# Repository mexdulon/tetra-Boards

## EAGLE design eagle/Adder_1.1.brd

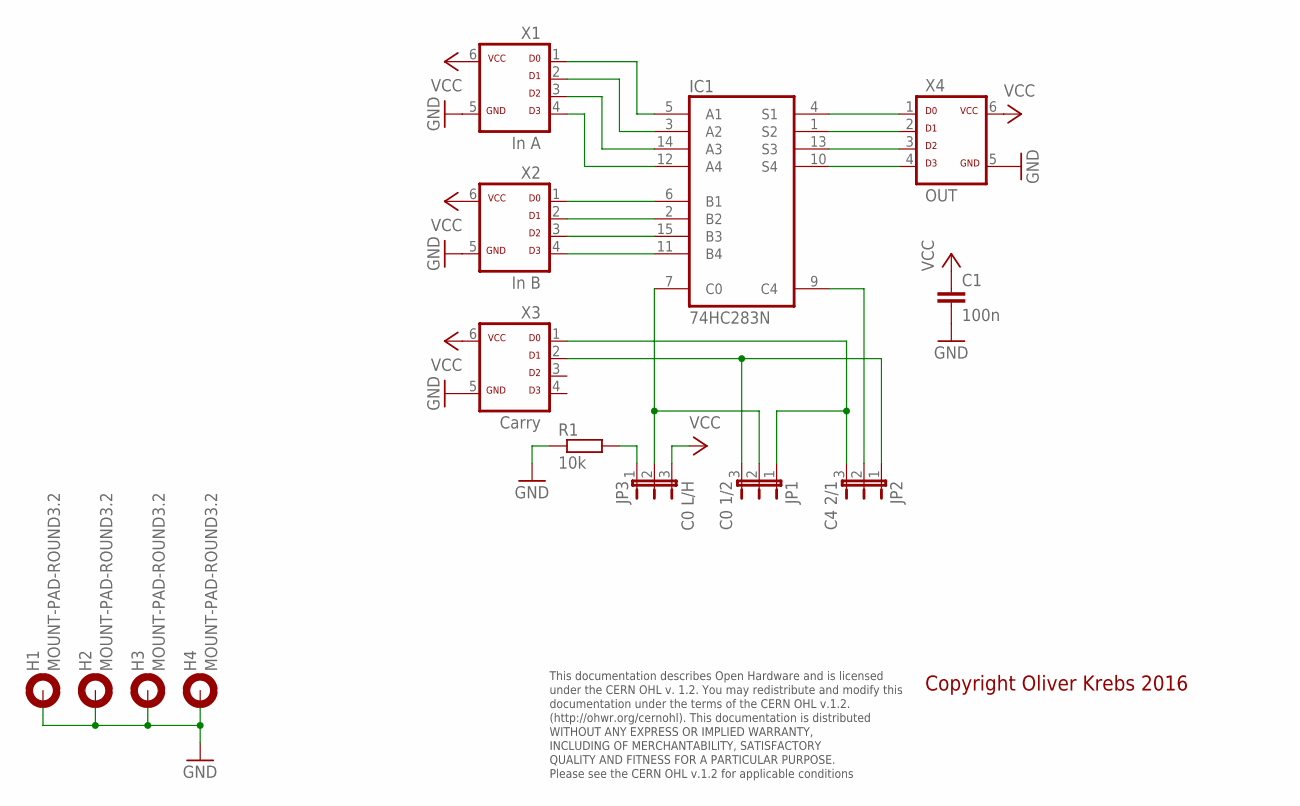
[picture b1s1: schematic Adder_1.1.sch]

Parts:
C1: 100n; C050-025X075
H1, H2, H3, H4: MOUNT-PAD-ROUND3.2; 3,2-PAD
IC1: 74HC283N; DIL16
JP1: C0 1/2; JP2
JP2: C4 2/1; JP2
JP3: C0 L/H; JP2
R1: 10k; 0207/10
X1: In A; ML-6
X2: In B; ML-6
X3: Carry; ML-6
X4: OUT; ML-6

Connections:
GND: C1.2, H1.B3,2, H2.B3,2, H3.B3,2, H4.B3,2, IC1.8 (GND), R1.1, X1.5, X2.5, X3.5, X4.5
unnamed: JP3.1, R1.2
unnamed: IC1.15 (B3), X2.3
unnamed: IC1.3 (A2), X1.2
unnamed: IC1.2 (B2), X2.2
unnamed: IC1.14 (A3), X1.3
unnamed: IC1.11 (B4), X2.4
unnamed: IC1.1 (S2), X4.2
unnamed: IC1.4 (S1), X4.1
unnamed: IC1.13 (S3), X4.3
unnamed: IC1.10 (S4), X4.4
unnamed: IC1.7 (C0), JP1.2, JP3.2
unnamed: IC1.9 (C4), JP2.2
unnamed: JP1.1, JP2.3, X3.1
unnamed: JP1.3, JP2.1, X3.2
unnamed: IC1.5 (A1), X1.1
unnamed: IC1.12 (A4), X1.4
unnamed: IC1.6 (B1), X2.1
VCC: C1.1, IC1.16 (VCC), JP3.3, X1.6, X2.6, X3.6, X4.6

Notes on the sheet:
This documentation describes Open Hardware and is licensed under the CERN OHL v. 1.2. You may redistribute and modify this documentation under the terms of the CERN OHL v.1.2. (http://ohwr.org/cernohl). This documentation is distributed WITHOUT ANY EXPRESS OR IMPLIED WARRANTY, INCLUDING OF MERCHANT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
Copyright Oliver Krebs 2016

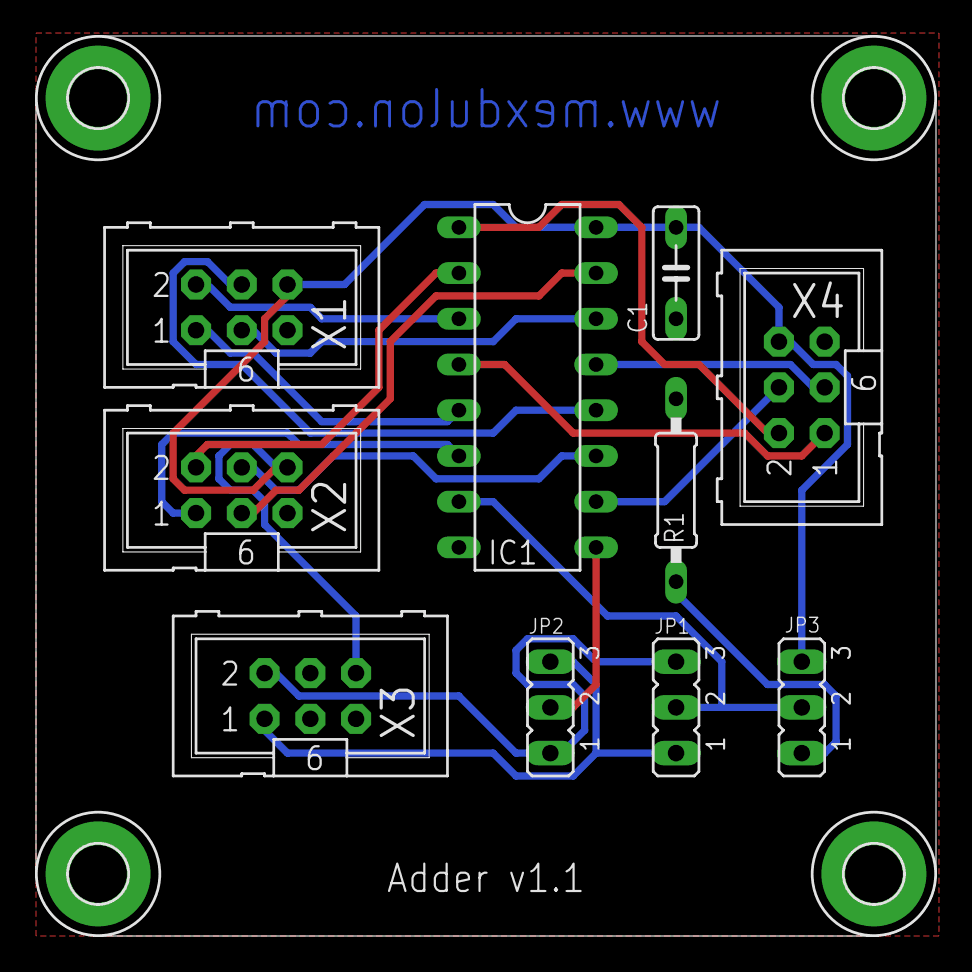
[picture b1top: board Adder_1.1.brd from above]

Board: 2 copper layers, 50.0 x 50.0 mm, 14 parts (0 on the bottom side), 19 nets.

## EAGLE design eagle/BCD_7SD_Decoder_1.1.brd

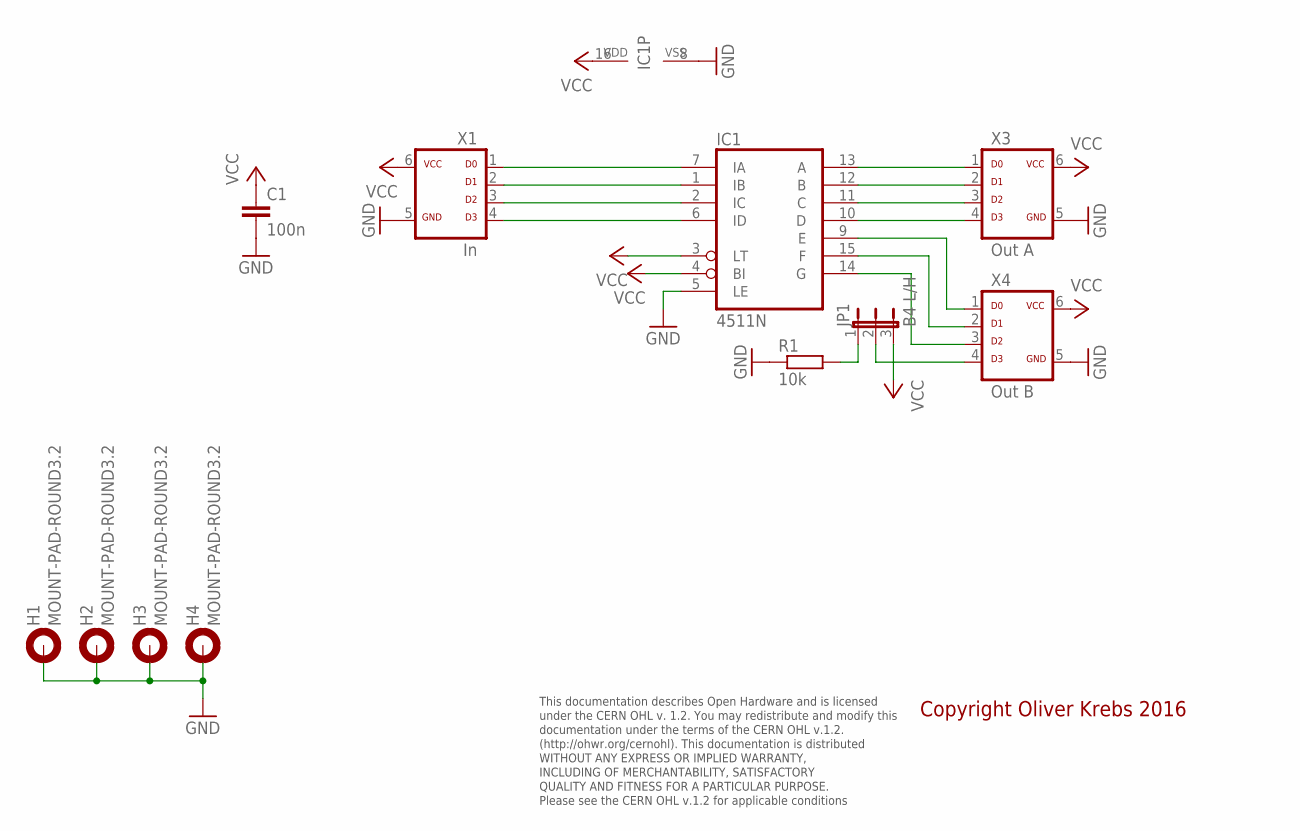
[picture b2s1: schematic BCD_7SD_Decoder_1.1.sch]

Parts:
C1: 100n; C050-025X075
H1, H2, H3, H4: MOUNT-PAD-ROUND3.2; 3,2-PAD
IC1: 4511N; DIL16
JP1: B4 L/H; JP2
R1: 10k; 0207/10
X1: In; ML-6
X3: Out A; ML-6
X4: Out B; ML-6

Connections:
GND: C1.2, H1.B3,2, H2.B3,2, H3.B3,2, H4.B3,2, IC1.5 (LE), IC1.8 (VSS), R1.1, X1.5, X3.5, X4.5
unnamed: IC1.7 (IA), X1.1
unnamed: IC1.1 (IB), X1.2
unnamed: IC1.2 (IC), X1.3
unnamed: IC1.6 (ID), X1.4
unnamed: IC1.13 (A), X3.1
unnamed: IC1.12 (B), X3.2
unnamed: IC1.11 (C), X3.3
unnamed: IC1.10 (D), X3.4
unnamed: IC1.9 (E), X4.1
unnamed: IC1.15 (F), X4.2
unnamed: IC1.14 (G), X4.3
unnamed: JP1.2, X4.4
unnamed: JP1.1, R1.2
VCC: C1.1, IC1.3 (LT), IC1.4 (BI), IC1.16 (VDD), JP1.3, X1.6, X3.6, X4.6

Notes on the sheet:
This documentation describes Open Hardware and is licensed under the CERN OHL v. 1.2. You may redistribute and modify this documentation under the terms of the CERN OHL v.1.2. (http://ohwr.org/cernohl). This documentation is distributed WITHOUT ANY EXPRESS OR IMPLIED WARRANTY, INCLUDING OF MERCHANT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
Copyright Oliver Krebs 2016

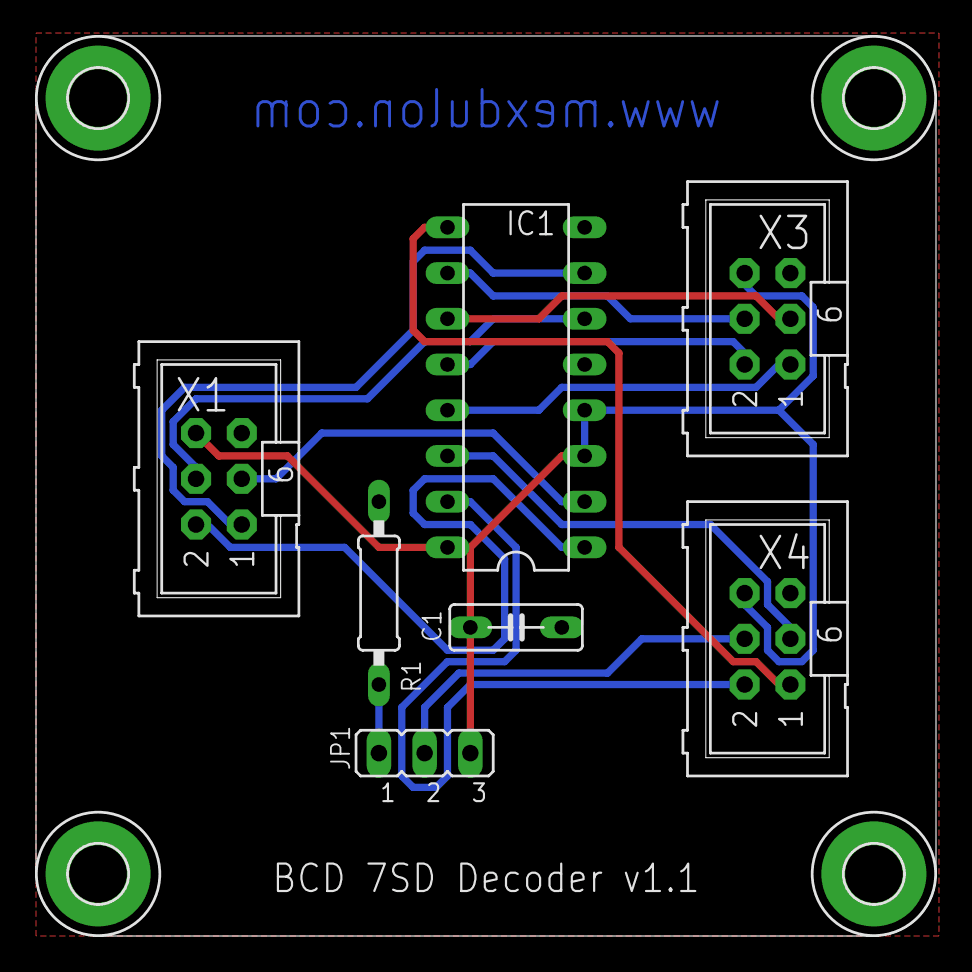
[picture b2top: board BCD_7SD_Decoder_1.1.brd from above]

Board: 2 copper layers, 50.0 x 50.0 mm, 11 parts (0 on the bottom side), 15 nets.

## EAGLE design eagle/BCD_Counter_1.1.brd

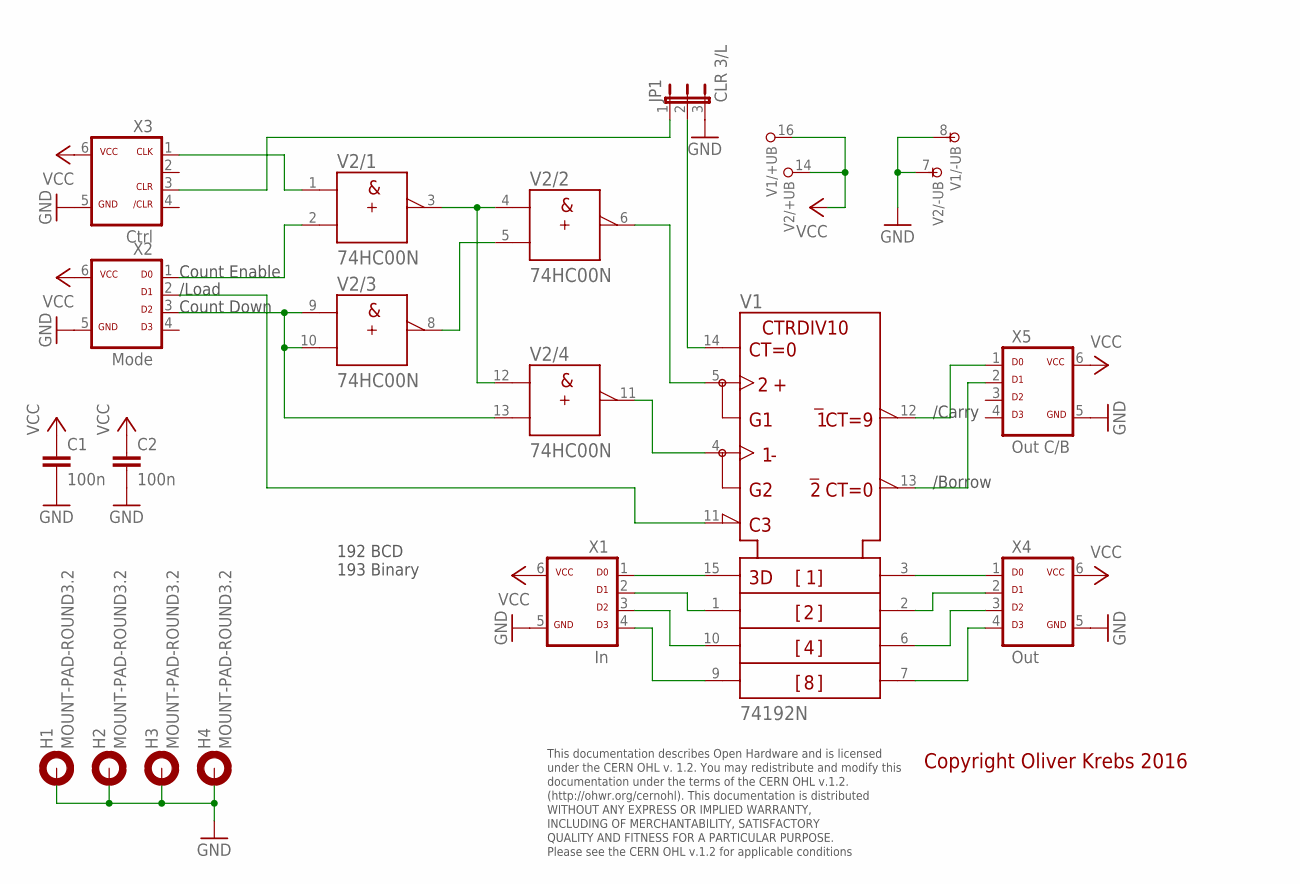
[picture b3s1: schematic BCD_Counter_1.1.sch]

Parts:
C1, C2: 100n; C050-025X075
H1, H2, H3, H4: MOUNT-PAD-ROUND3.2; 3,2-PAD
JP1: CLR 3/L; JP2
V1: 74192N; DIL16
V2: 74HC00N; DIL14
X1: In; ML-6
X2: Mode; ML-6
X3: Ctrl; ML-6
X4: Out; ML-6
X5: Out C/B; ML-6

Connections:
GND: C1.2, C2.2, H1.B3,2, H2.B3,2, H3.B3,2, H4.B3,2, JP1.3, V1.8 (-UB), V2.7 (-UB), X1.5, X2.5, X3.5, X4.5, X5.5
unnamed: V1.15 (A), X1.1
unnamed: V1.1 (B), X1.2
unnamed: V1.10 (C), X1.3
unnamed: V1.9 (D), X1.4
unnamed: V1.3 (QA), X4.1
unnamed: V1.2 (QB), X4.2
unnamed: V1.6 (QC), X4.3
unnamed: V1.7 (QD), X4.4
unnamed: V1.13 (!BO), X5.2
unnamed: V1.12 (!CO), X5.1
unnamed: V2.1 (A), X3.1
unnamed: V2.5 (B), V2.8 (Y)
unnamed: V2.3 (Y), V2.4 (A), V2.12 (A)
unnamed: V1.5 (UP), V2.6 (Y)
unnamed: V1.4 (DOWN), V2.11 (Y)
unnamed: JP1.2, V1.14 (CLR)
unnamed: V2.9 (A), V2.10 (B), V2.13 (B), X2.3
unnamed: V2.2 (B), X2.1
unnamed: V1.11 (!LOAD), X2.2
unnamed: JP1.1, X3.3
VCC: C1.1, C2.1, V1.16 (+UB), V2.14 (+UB), X1.6, X2.6, X3.6, X4.6, X5.6

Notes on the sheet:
Count Down
Count Enable
/Load
/Carry
/Borrow
192 BCD 193 Binary
This documentation describes Open Hardware and is licensed under the CERN OHL v. 1.2. You may redistribute and modify this documentation under the terms of the CERN OHL v.1.2. (http://ohwr.org/cernohl). This documentation is distributed WITHOUT ANY EXPRESS OR IMPLIED WARRANTY, INCLUDING OF MERCHANT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
Copyright Oliver Krebs 2016

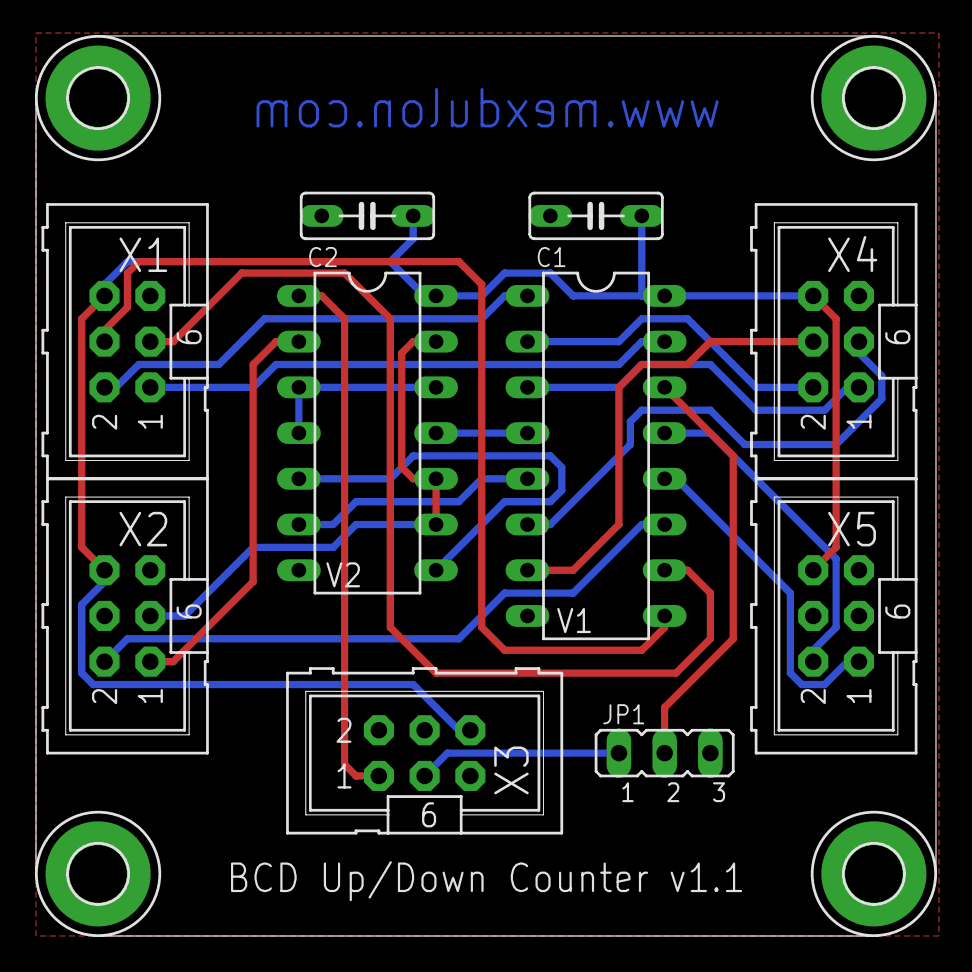
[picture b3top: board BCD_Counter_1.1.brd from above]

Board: 2 copper layers, 50.0 x 50.0 mm, 14 parts (0 on the bottom side), 22 nets.

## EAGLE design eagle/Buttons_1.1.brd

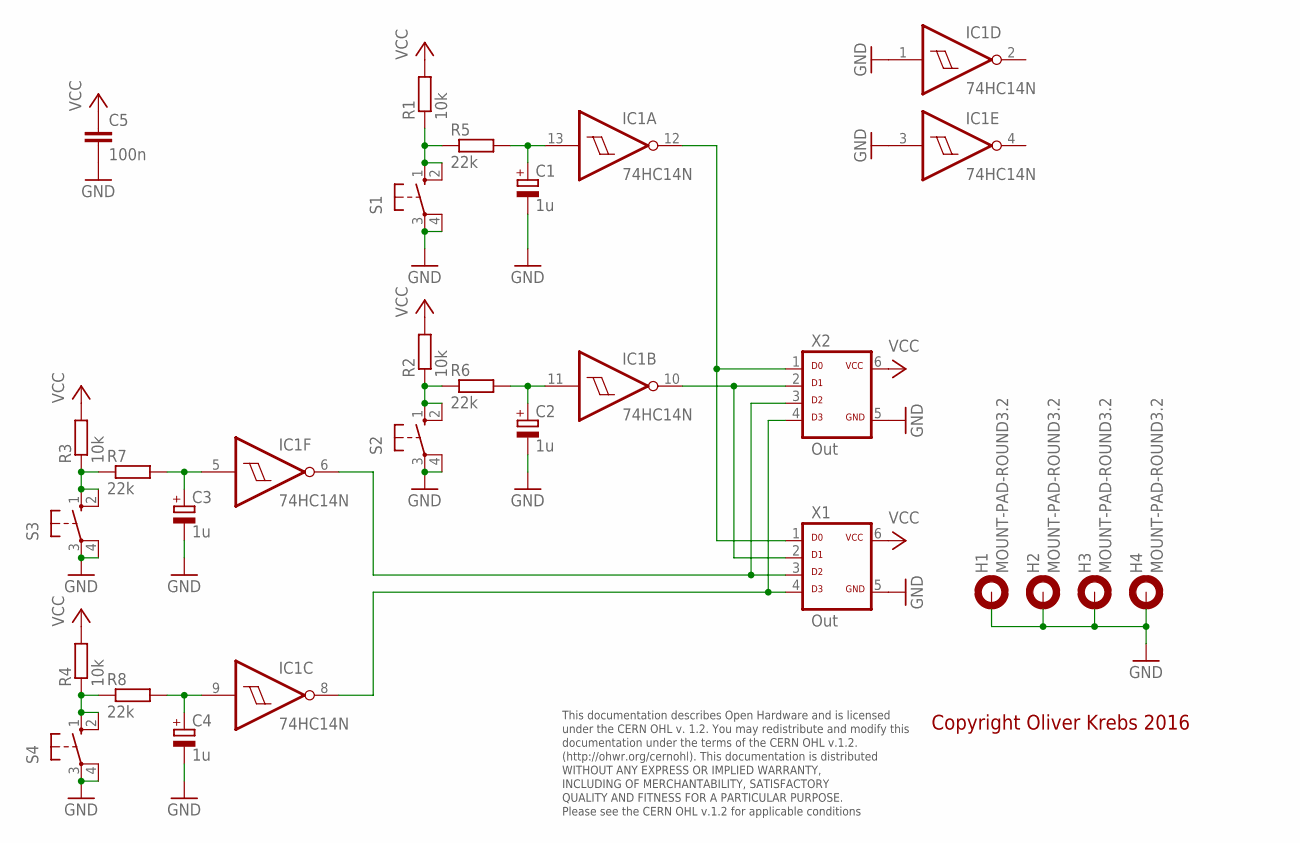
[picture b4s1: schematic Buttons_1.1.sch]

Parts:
C1, C2, C3, C4: 1u; E2-5
C5: 100n; C050-025X075
H1, H2, H3, H4: MOUNT-PAD-ROUND3.2; 3,2-PAD
IC1: 74HC14N; DIL14
R1, R2, R3, R4: 10k; 0207/10
R5, R6, R7, R8: 22k; 0207/10
S1, S2, S3, S4: 10-XX; B3F-10XX
X1, X2: Out; ML-6

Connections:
GND: C1.-, C2.-, C3.-, C4.-, C5.2, H1.B3,2, H2.B3,2, H3.B3,2, H4.B3,2, IC1.1 (I), IC1.3 (I), IC1.7 (GND), S1.3, S1.4 (P1), S2.3, S2.4 (P1), S3.3, S3.4 (P1), S4.3, S4.4 (P1), X1.5, X2.5
unnamed: IC1.12 (O), X1.1, X2.1
unnamed: IC1.10 (O), X1.2, X2.2
unnamed: IC1.6 (O), X1.3, X2.3
unnamed: R3.1, R7.1, S3.1 (S), S3.2 (S1)
unnamed: C3.+, IC1.5 (I), R7.2
unnamed: IC1.8 (O), X1.4, X2.4
unnamed: R4.1, R8.1, S4.1 (S), S4.2 (S1)
unnamed: C4.+, IC1.9 (I), R8.2
unnamed: R2.1, R6.1, S2.1 (S), S2.2 (S1)
unnamed: C2.+, IC1.11 (I), R6.2
unnamed: R1.1, R5.1, S1.1 (S), S1.2 (S1)
unnamed: C1.+, IC1.13 (I), R5.2
VCC: C5.1, IC1.14 (VCC), R1.2, R2.2, R3.2, R4.2, X1.6, X2.6

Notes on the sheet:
This documentation describes Open Hardware and is licensed under the CERN OHL v. 1.2. You may redistribute and modify this documentation under the terms of the CERN OHL v.1.2. (http://ohwr.org/cernohl). This documentation is distributed WITHOUT ANY EXPRESS OR IMPLIED WARRANTY, INCLUDING OF MERCHANT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
Copyright Oliver Krebs 2016

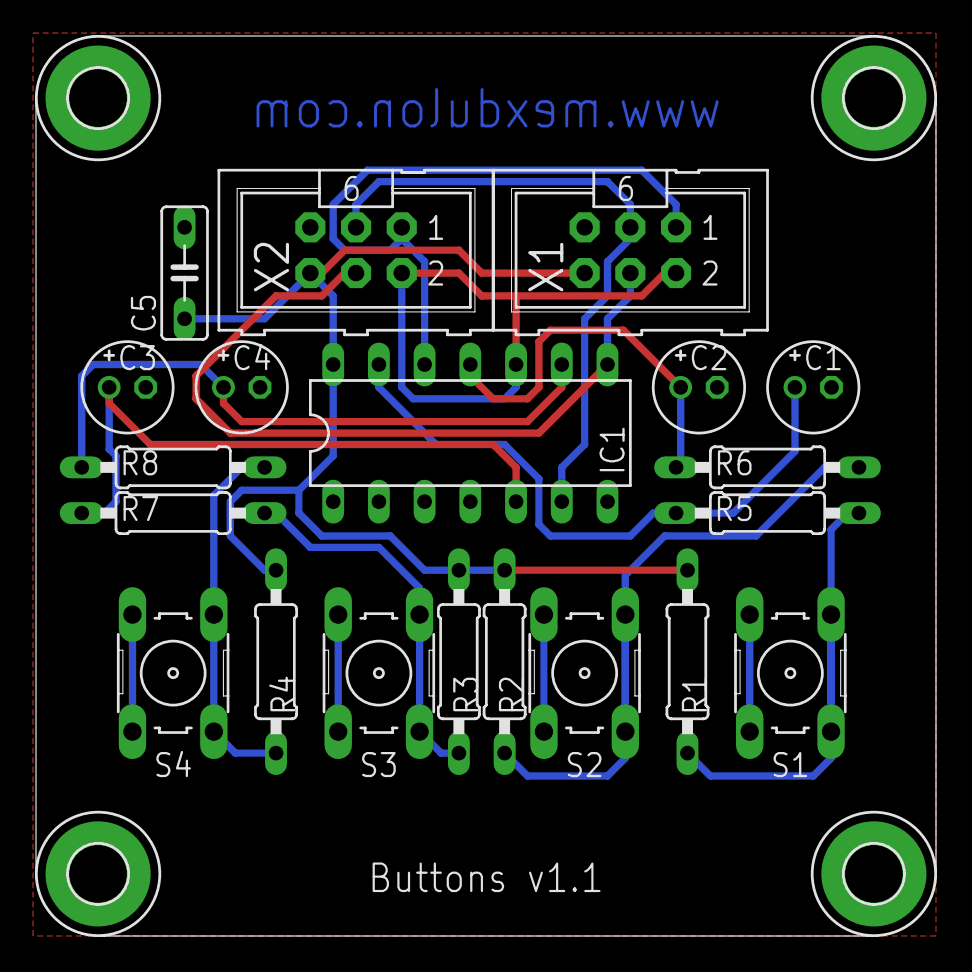
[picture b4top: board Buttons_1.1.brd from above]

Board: 2 copper layers, 50.0 x 50.0 mm, 24 parts (0 on the bottom side), 14 nets.

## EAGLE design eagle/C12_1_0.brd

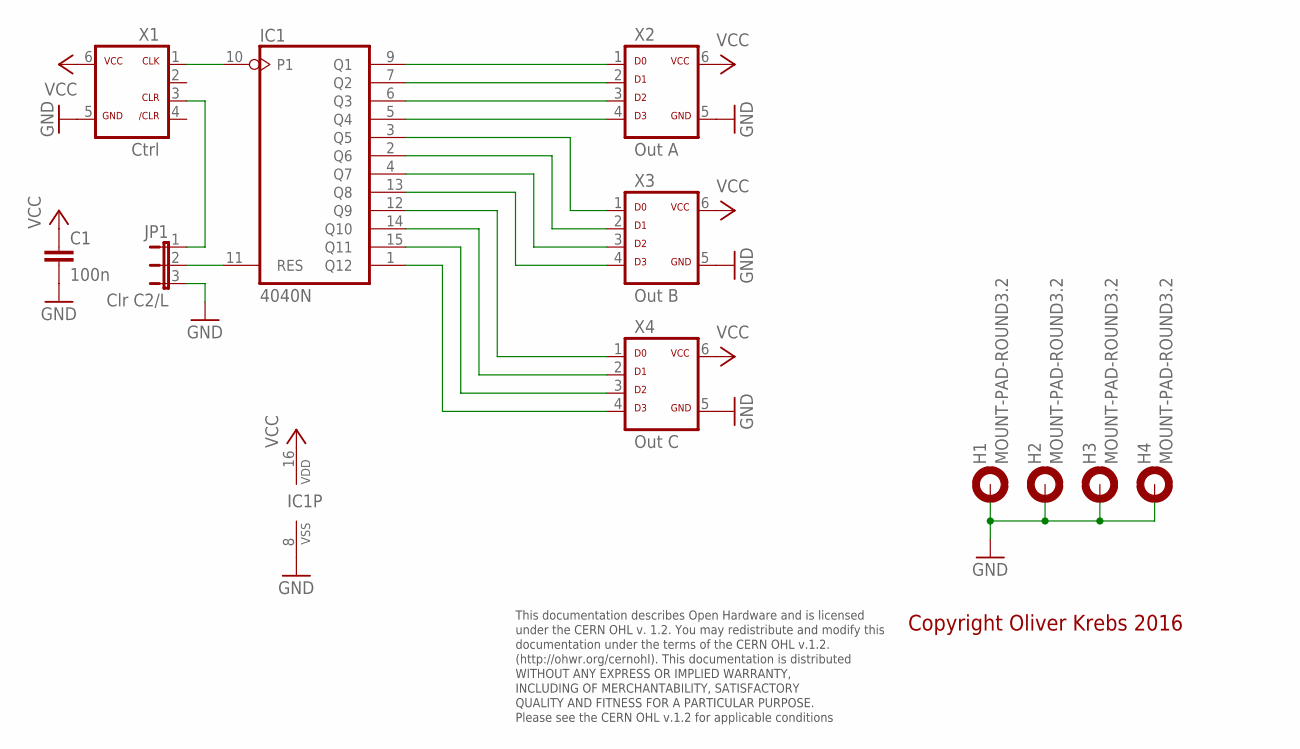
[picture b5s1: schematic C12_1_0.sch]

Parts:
C1: 100n; C050-025X075
H1, H2, H3, H4: MOUNT-PAD-ROUND3.2; 3,2-PAD
IC1: 4040N; DIL16
JP1: Clr C2/L; JP2
X1: Ctrl; ML-6
X2: Out A; ML-6
X3: Out B; ML-6
X4: Out C; ML-6

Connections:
GND: C1.2, H1.B3,2, H2.B3,2, H3.B3,2, H4.B3,2, IC1.8 (VSS), JP1.3, X1.5, X2.5, X3.5, X4.5
unnamed: IC1.9 (Q1), X2.1
unnamed: IC1.7 (Q2), X2.2
unnamed: IC1.6 (Q3), X2.3
unnamed: IC1.5 (Q4), X2.4
unnamed: IC1.12 (Q9), X4.1
unnamed: IC1.14 (Q10), X4.2
unnamed: IC1.15 (Q11), X4.3
unnamed: IC1.1 (Q12), X4.4
unnamed: IC1.10 (P1), X1.1
unnamed: JP1.1, X1.3
unnamed: IC1.11 (RES), JP1.2
unnamed: IC1.3 (Q5), X3.1
unnamed: IC1.2 (Q6), X3.2
unnamed: IC1.4 (Q7), X3.3
unnamed: IC1.13 (Q8), X3.4
VCC: C1.1, IC1.16 (VDD), X1.6, X2.6, X3.6, X4.6

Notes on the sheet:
This documentation describes Open Hardware and is licensed under the CERN OHL v. 1.2. You may redistribute and modify this documentation under the terms of the CERN OHL v.1.2. (http://ohwr.org/cernohl). This documentation is distributed WITHOUT ANY EXPRESS OR IMPLIED WARRANTY, INCLUDING OF MERCHANT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
Copyright Oliver Krebs 2016

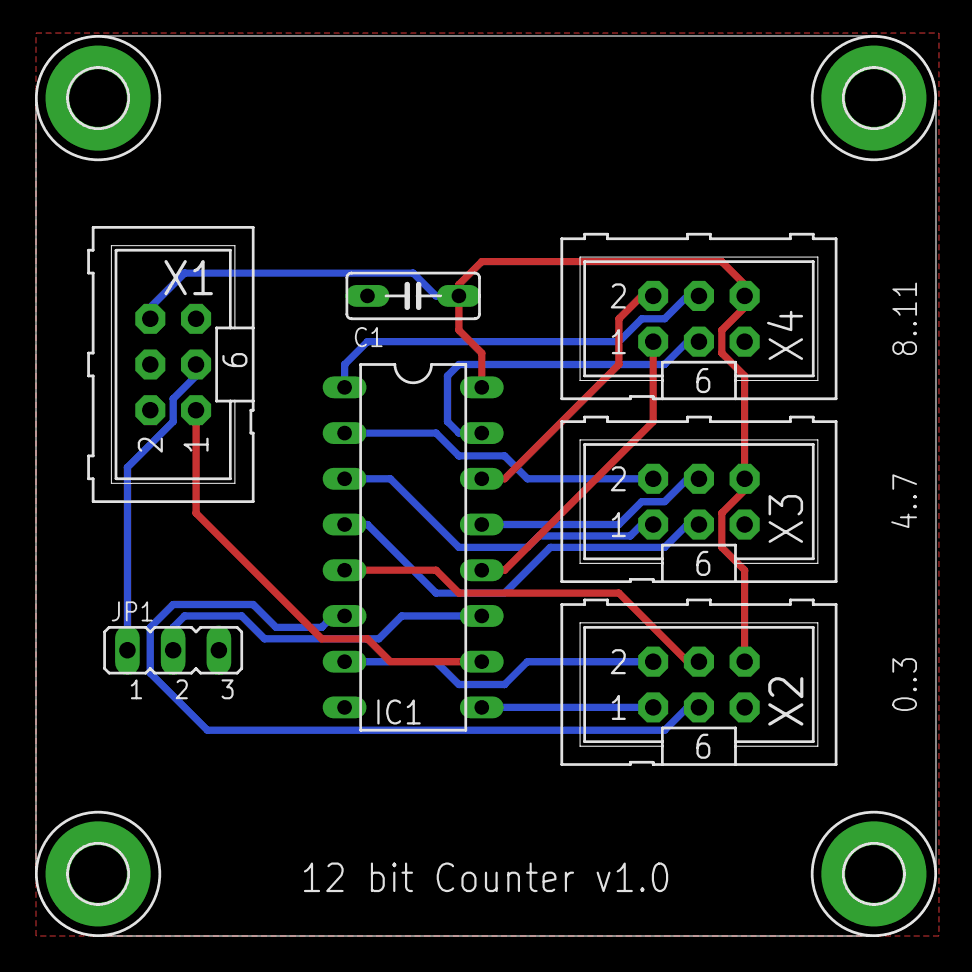
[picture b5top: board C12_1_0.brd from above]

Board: 2 copper layers, 50.0 x 50.0 mm, 11 parts (0 on the bottom side), 17 nets.

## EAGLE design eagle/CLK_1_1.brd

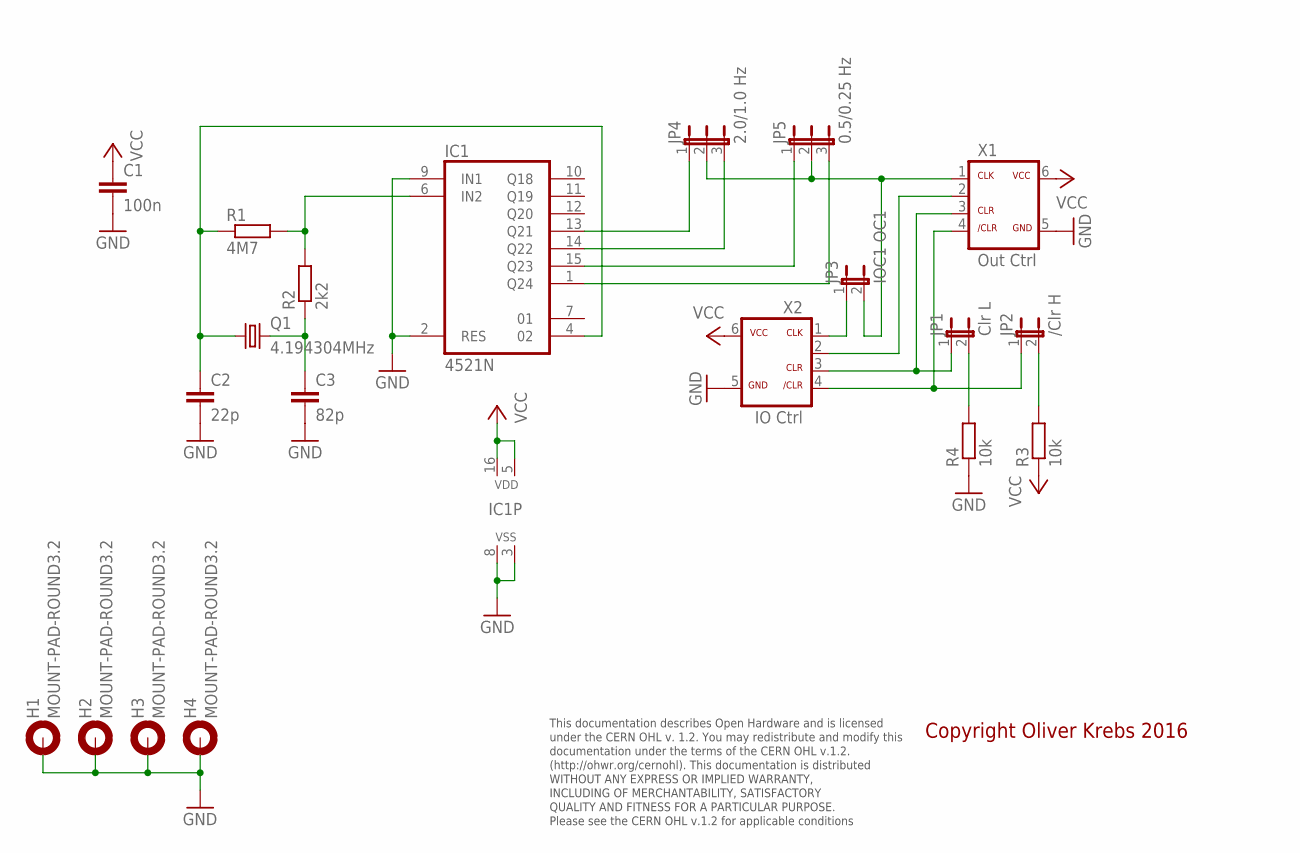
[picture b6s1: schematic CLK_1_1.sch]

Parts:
C1: 100n; C050-025X075
C2: 22p; C050-025X075
C3: 82p; C050-025X075
H1, H2, H3, H4: MOUNT-PAD-ROUND3.2; 3,2-PAD
IC1: 4521N; DIL16
JP1: Clr L; JP1
JP2: /Clr H; JP1
JP3: IOC1 OC1; JP1
JP4: 2.0/1.0 Hz; JP2-U
JP5: 0.5/0.25 Hz; JP2-U
Q1: 4.194304MHz; HC49US
R1: 4M7; 0207/10
R2: 2k2; 0207/10
R3, R4: 10k; 0207/10
X1: Out Ctrl; ML-6
X2: IO Ctrl; ML-6

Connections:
GND: C1.2, C2.2, C3.2, H1.B3,2, H2.B3,2, H3.B3,2, H4.B3,2, IC1.2 (RES), IC1.3 (VSS), IC1.8 (VSS), IC1.9 (IN1), R4.1, X1.5, X2.5
unnamed: C3.1, Q1.2, R2.1
unnamed: C2.1, IC1.4 (02), Q1.1, R1.1
unnamed: IC1.6 (IN2), R1.2, R2.2
unnamed: IC1.14 (Q22), JP4.3
unnamed: IC1.13 (Q21), JP4.1
unnamed: IC1.15 (Q23), JP5.1
unnamed: IC1.1 (Q24), JP5.3
unnamed: JP3.2, JP4.2, JP5.2, X1.1
unnamed: JP2.2, R3.2
unnamed: JP1.1, X1.3, X2.3
unnamed: JP2.1, X1.4, X2.4
unnamed: JP1.2, R4.2
unnamed: JP3.1, X2.1
VCC: C1.1, IC1.5 (VDD), IC1.16 (VDD), R3.1, X1.6, X2.6
X2: X1.2, X2.2

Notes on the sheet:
This documentation describes Open Hardware and is licensed under the CERN OHL v. 1.2. You may redistribute and modify this documentation under the terms of the CERN OHL v.1.2. (http://ohwr.org/cernohl). This documentation is distributed WITHOUT ANY EXPRESS OR IMPLIED WARRANTY, INCLUDING OF MERCHANT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
Copyright Oliver Krebs 2016

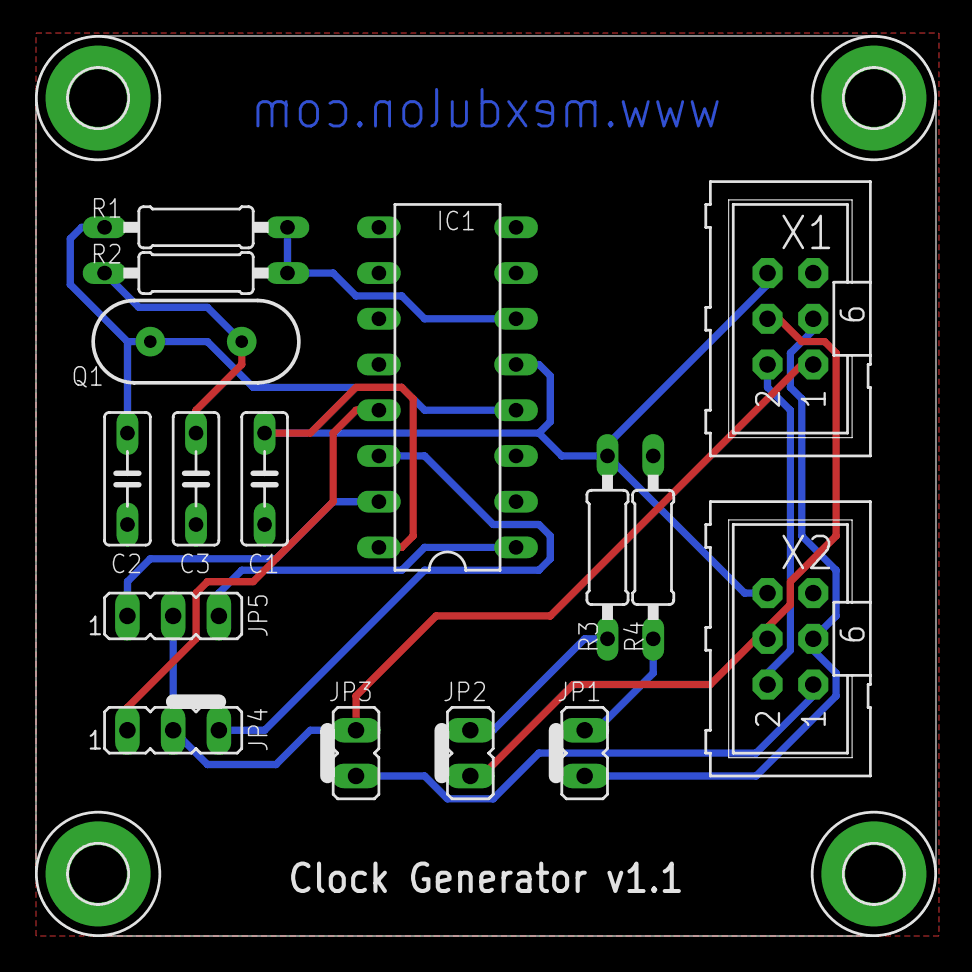
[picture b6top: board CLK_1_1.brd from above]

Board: 2 copper layers, 50.0 x 50.0 mm, 20 parts (0 on the bottom side), 16 nets.

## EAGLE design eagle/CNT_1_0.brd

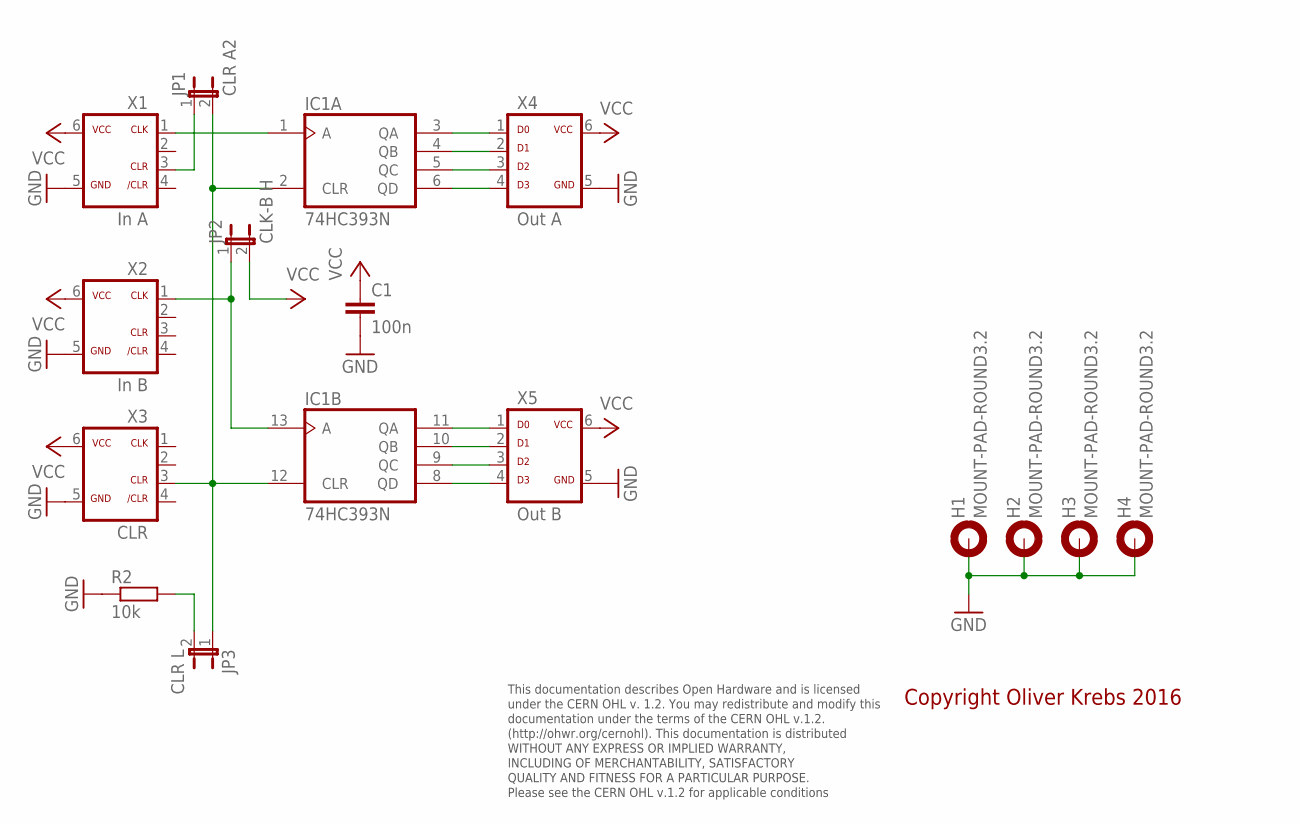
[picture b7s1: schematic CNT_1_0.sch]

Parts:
C1: 100n; C050-025X075
H1, H2, H3, H4: MOUNT-PAD-ROUND3.2; 3,2-PAD
IC1: 74HC393N; DIL14
JP1: CLR A2; JP1
JP2: CLK-B H; JP1
JP3: CLR L; JP1
R2: 10k; 0207/10
X1: In A; ML-6
X2: In B; ML-6
X3: CLR; ML-6
X4: Out A; ML-6
X5: Out B; ML-6

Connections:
GND: C1.2, H1.B3,2, H2.B3,2, H3.B3,2, H4.B3,2, IC1.7 (GND), R2.1, X1.5, X2.5, X3.5, X4.5, X5.5
unnamed: IC1.3 (QA), X4.1
unnamed: IC1.4 (QB), X4.2
unnamed: IC1.5 (QC), X4.3
unnamed: IC1.6 (QD), X4.4
unnamed: IC1.1 (A), X1.1
unnamed: JP1.1, X1.3
unnamed: IC1.2 (CLR), IC1.12 (CLR), JP1.2, JP3.1, X3.3
unnamed: IC1.13 (A), JP2.1, X2.1
unnamed: IC1.11 (QA), X5.1
unnamed: IC1.10 (QB), X5.2
unnamed: IC1.9 (QC), X5.3
unnamed: IC1.8 (QD), X5.4
unnamed: JP3.2, R2.2
VCC: C1.1, IC1.14 (VCC), JP2.2, X1.6, X2.6, X3.6, X4.6, X5.6

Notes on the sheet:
This documentation describes Open Hardware and is licensed under the CERN OHL v. 1.2. You may redistribute and modify this documentation under the terms of the CERN OHL v.1.2. (http://ohwr.org/cernohl). This documentation is distributed WITHOUT ANY EXPRESS OR IMPLIED WARRANTY, INCLUDING OF MERCHANT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
Copyright Oliver Krebs 2016

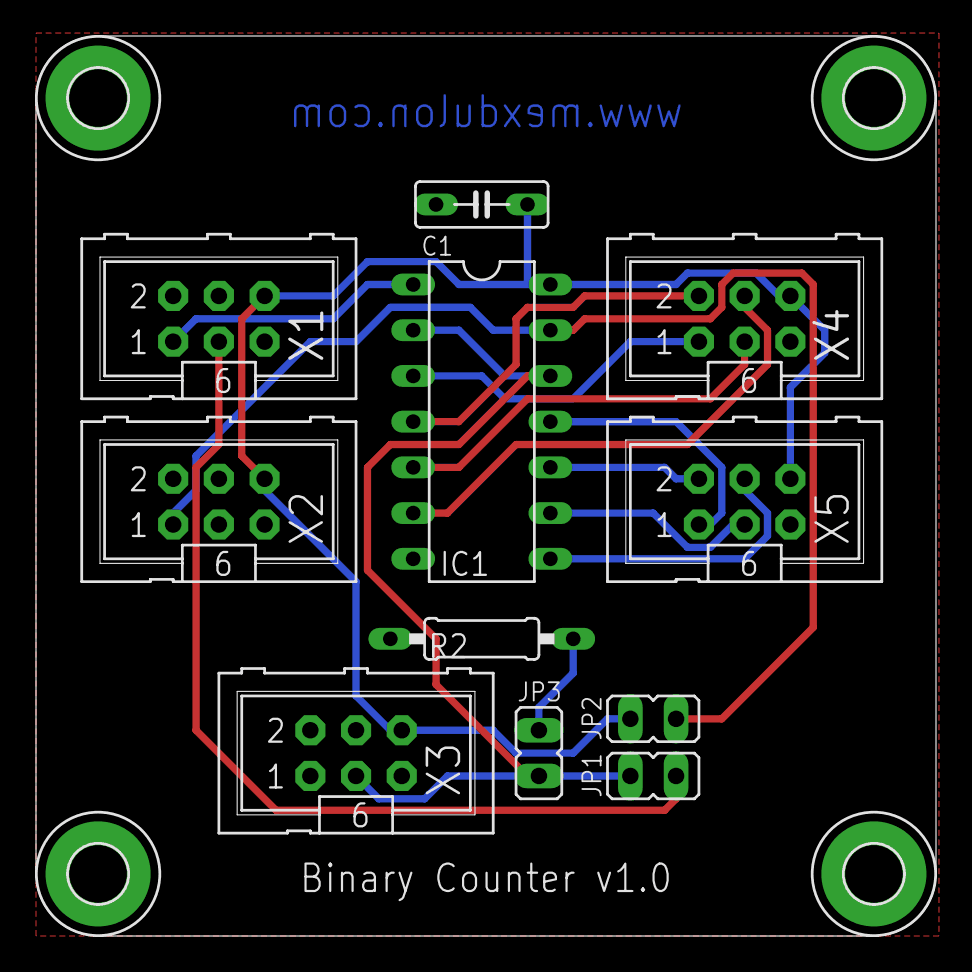
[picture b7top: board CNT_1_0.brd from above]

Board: 2 copper layers, 50.0 x 50.0 mm, 15 parts (0 on the bottom side), 15 nets.

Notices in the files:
eagle/Adder_1.1.brd:
Licensed under CERN OHL v.1.2
parts and their libraries:
SparkFun-FreqCtrl: Licensing: Creative Commons ShareAlike 4.0 International - https://creativecommons.org/licenses/by-sa/4.0
